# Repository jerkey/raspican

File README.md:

# raspican
##raspberry pi CANbus hardware in kicad

README.md for raspican Hardware
Files .pro .sch and .kicad_pcb in KiCAD format
License CC BY-SA 3.0
raspican Hardware

how to setup cansend software on the raspberry pi:
-------------------------------------------------
http://skpang.co.uk/blog/archives/1165

_Inspired by retired PICAN project at:_

http://skpang.co.uk/catalog/pican-canbus-board-retired-replacement-available-p-1196.html

````
22:54 < jerkey_> http://www.cowfishstudios.com/blog/canned-pi-part1
23:25 <@amatus> this stuff is out of date
23:25 <@amatus> this is what i did:
23:26 <@amatus> sudo apt-get install can-utils
23:26 <@amatus> echo dtoverlay=mcp2515-can0,oscillator=16000000,interrupt=25 >> /boot/config.txt
23:27 <@amatus> reboot
23:36 <@amatus> scratch that, echo dtoverlay=mcp2515-can0 >> /boot/config.txt
23:40 < jerkey_> https://github.com/jerkey/raspican
23:50 <@amatus> then follow the ip ... commands
Day changed to 14 Mar 2017
00:56 < jerkey_> i bet your car wasn't spitting rhymes where it was supposed to.  i can't find anything wrong with this hardware!
````

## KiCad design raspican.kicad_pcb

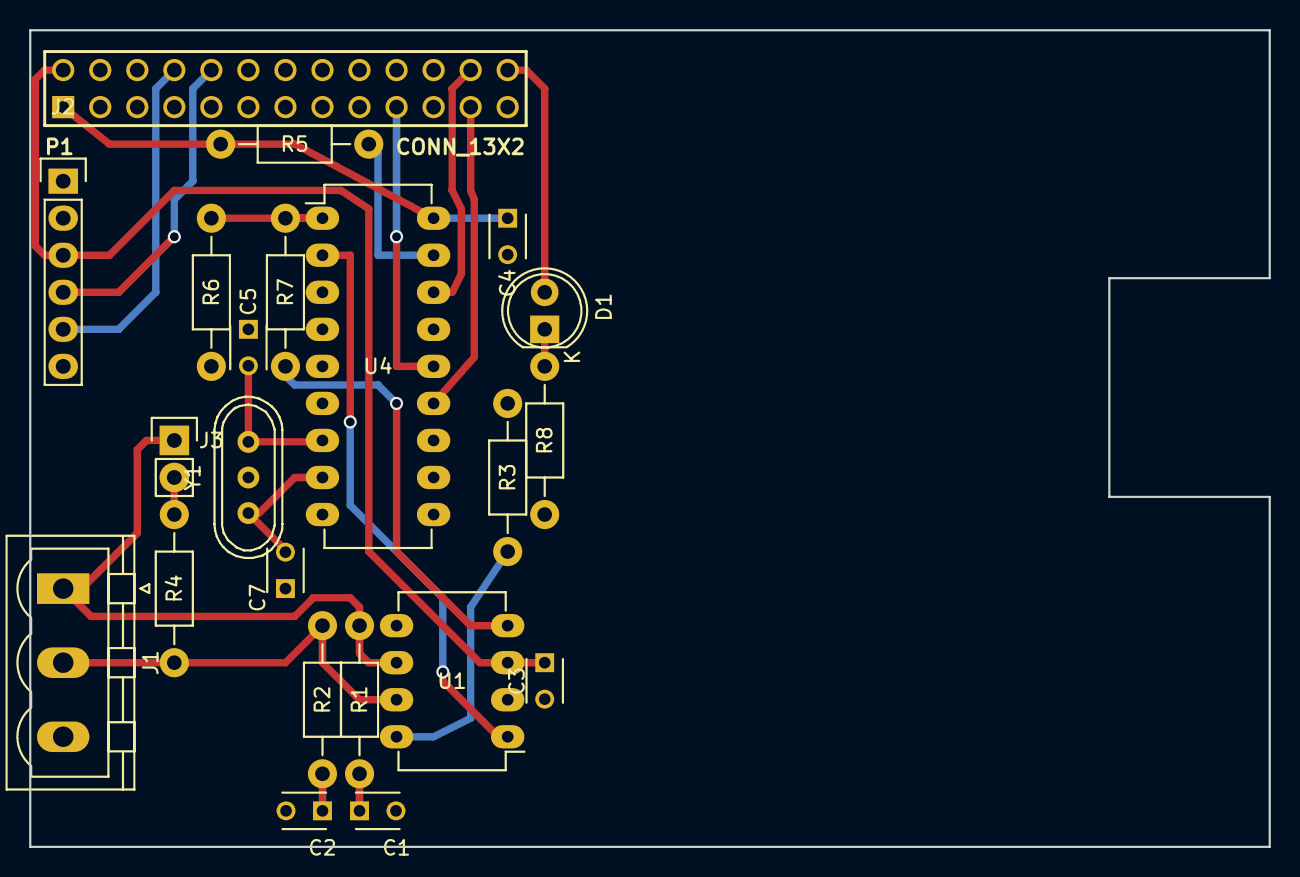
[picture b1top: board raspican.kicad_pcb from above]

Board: 2 copper layers, 85.0 x 56.0 mm, 22 parts (0 on the bottom side), 24 nets.

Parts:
C1, C2: 560pF; C_Disc_D3_P2.5
C3, C4: 0.1μF; C_Disc_D3_P2.5
C5, C7: 22pF; C_Disc_D3_P2.5
D1: LED; LED-5MM
J1: CANBUS; PhoenixContact_MSTBVA-G_03x5.08mm_Vertical
J2: TTL_SERIAL; Pin_Header_Straight_1x06
J3: TERMINATE; Pin_Header_Straight_1x02
P1: CONN_13X2; pin_array_13x2
R1, R2: 100Ω; Resistor_Horizontal_RM10mm
R3, R5: 4K7Ω; Resistor_Horizontal_RM10mm
R4: 120Ω; Resistor_Horizontal_RM10mm
R6: 18KΩ; Resistor_Horizontal_RM10mm
R7: 10KΩ; Resistor_Horizontal_RM10mm
R8: 1KΩ; Resistor_Horizontal_RM10mm
U1: MCP2551-I/P; DIP-8_W7.62mm_LongPads
U4: MCP2515; DIP-18_W7.62mm_LongPads
Y1: 16MHz; Crystal_HC49-U_Vertical_3Pin

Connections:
+3.3V: C4.1, P1.1, R5.1, U4.18
+5V: C3.1, J2.3, P1.2, U1.3
/CANH: J1.2, R2.1, R4.1, U1.7
/CANL: J1.1, J3.1, R1.1, U1.6
/GPIO7(CE1): D1.2, P1.26
/GPIO8(CE0): P1.24, U4.16
/GPIO9(MISO): P1.21, U4.15
/GPIO10(MOSI): P1.19, U4.14
/GPIO11(SCLK): P1.23, U4.13
/GPIO25: P1.22, U4.12
/RXD: J2.4, P1.10
/TXD: J2.5, P1.8
GND: C1.2, C2.2, C3.2, C4.2, C5.1, C7.1, J1.3, J2.1, J2.2, P1.6, R3.1, R6.2, R8.1, U1.2, U4.9, Y1.3
unnamed: C1.1, R1.2
unnamed: C2.1, R2.2
unnamed: C5.2, U4.7, Y1.2
unnamed: C7.2, U4.8, Y1.1
unnamed: D1.1, R8.2
unnamed: J3.2, R4.2
unnamed: R3.2, U1.8
unnamed: R5.2, U4.17
unnamed: R6.1, R7.2, U4.1
unnamed: R7.1, U1.4
unnamed: U1.1, U4.2

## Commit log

2017-03-03 start wiring stuff up
2017-03-03 add .gitignore
2017-03-03 add readme
2017-03-03 replace mcp2515 with correct DIP/SOIC pinout
2017-03-03 finished schematic, ready to make a board
2017-03-03 add schematic of original pican board for reference
2017-03-04 remove special library from project
2017-03-04 assign through-hole footprints to all parts
2017-03-04 change crystal in schematic to have ground on pin 3
2017-03-04 place most parts, fix grid
2017-03-04 update README.md with link to software setup for pi, corrected a URL
2017-03-04 move footprints around, aligned with grid
2017-03-04 add picture of the board so far
2017-03-07 add custom trace widths and start running traces
2017-03-07 ok i ran all the traces except ground. and no more buttons.
2017-03-14 finish running traces on the board
2017-03-14 template was wrong about P1 connections
2017-03-14 store notes from trying it
2017-03-14 readmeability
